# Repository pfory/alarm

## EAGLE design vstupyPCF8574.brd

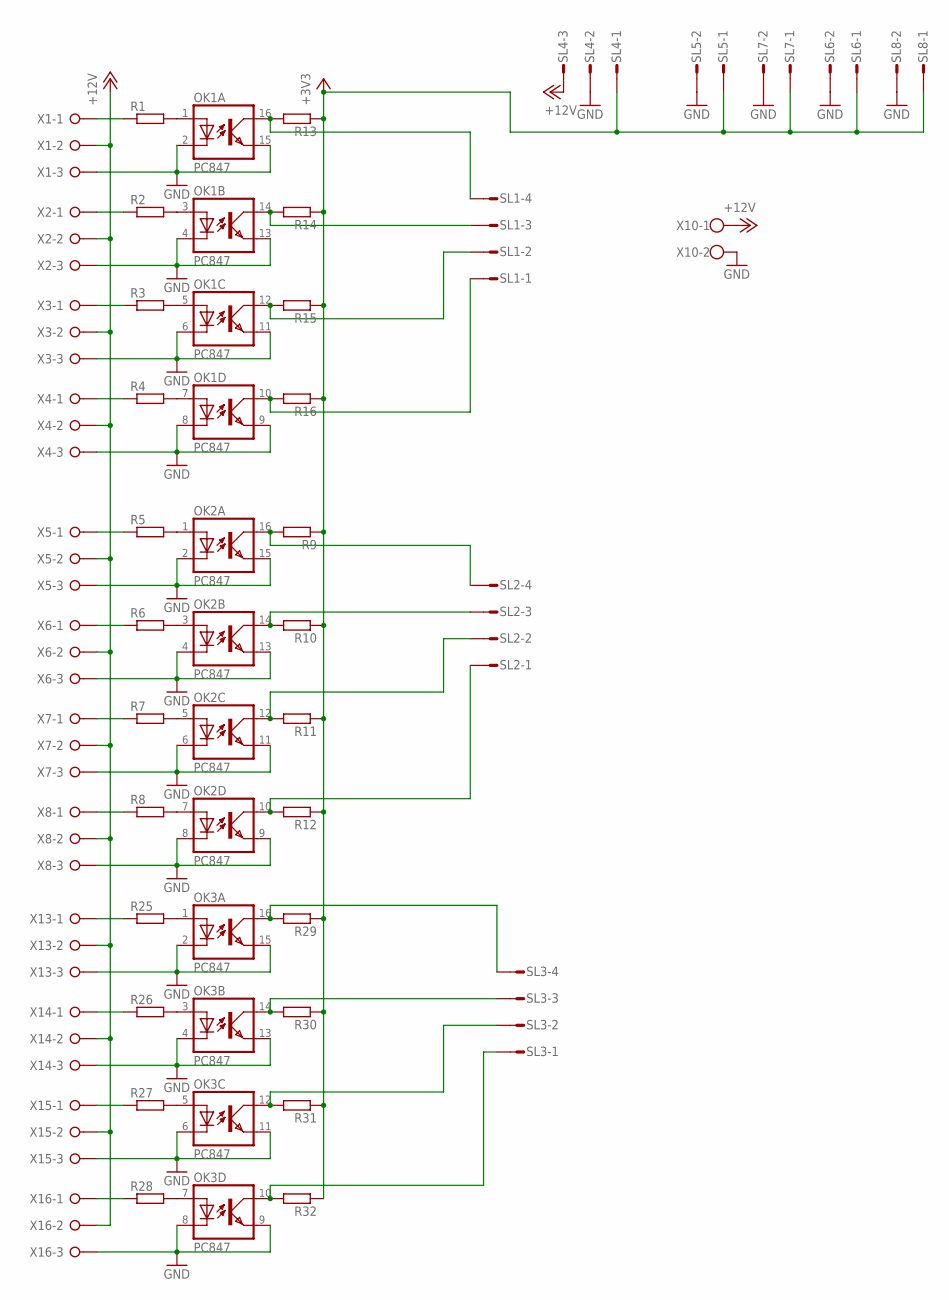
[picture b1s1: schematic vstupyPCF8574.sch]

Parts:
OK1, OK2, OK3: PC847; DIL16
R1, R2, R3, R4, R5, R6, R7, R8, R9, R10, R11, R12, R13, R14, R15, R16, R25, R26, R27, R28, R29, R30, R31, R32: R-EU_0204/5; 0204/5
SL1, SL2, SL3: M04S; 04P
SL4: M03S; 03P
SL5, SL6, SL7, SL8: M02S; 02P
X1, X2, X3, X4, X5, X6, X7, X8, X13, X14, X15, X16: W237-3E
X10: W237-102

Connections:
+3V3: R9.1, R10.1, R11.1, R12.1, R13.1, R14.1, R15.1, R16.1, R29.1, R30.1, R31.1, R32.1, SL4.1, SL5.1, SL6.1, SL7.1, SL8.1
+12V: SL4.3, X1.2, X2.2, X3.2, X4.2, X5.2, X6.2, X7.2, X8.2, X10.1, X13.2, X14.2, X15.2, X16.2
GND: OK1.2 (C), OK1.4 (C), OK1.6 (C), OK1.8 (C), OK1.9 (EMIT), OK1.11 (EMIT), OK1.13 (EMIT), OK1.15 (EMIT), OK2.2 (C), OK2.4 (C), OK2.6 (C), OK2.8 (C), OK2.9 (EMIT), OK2.11 (EMIT), OK2.13 (EMIT), OK2.15 (EMIT), OK3.2 (C), OK3.4 (C), OK3.6 (C), OK3.8 (C), OK3.9 (EMIT), OK3.11 (EMIT), OK3.13 (EMIT), OK3.15 (EMIT), SL4.2, SL5.2, SL6.2, SL7.2, SL8.2, X1.3, X2.3, X3.3, X4.3, X5.3, X6.3, X7.3, X8.3, X10.2, X13.3, X14.3, X15.3, X16.3
unnamed: OK1.1 (A), R1.2
unnamed: OK1.3 (A), R2.2
unnamed: OK1.5 (A), R3.2
unnamed: OK1.7 (A), R4.2
unnamed: OK2.1 (A), R5.2
unnamed: OK2.3 (A), R6.2
unnamed: OK2.5 (A), R7.2
unnamed: OK2.7 (A), R8.2
unnamed: R5.1, X5.1
unnamed: R6.1, X6.1
unnamed: R7.1, X7.1
unnamed: R8.1, X8.1
unnamed: R1.1, X1.1
unnamed: R2.1, X2.1
unnamed: R3.1, X3.1
unnamed: R4.1, X4.1
unnamed: OK2.16 (COL), R9.2, SL2.4
unnamed: OK2.14 (COL), R10.2, SL2.3
unnamed: OK2.12 (COL), R11.2, SL2.2
unnamed: OK2.10 (COL), R12.2, SL2.1
unnamed: OK1.16 (COL), R13.2, SL1.4
unnamed: OK1.14 (COL), R14.2, SL1.3
unnamed: OK1.12 (COL), R15.2, SL1.2
unnamed: OK3.16 (COL), R29.2, SL3.4
unnamed: OK3.14 (COL), R30.2, SL3.3
unnamed: OK3.12 (COL), R31.2, SL3.2
unnamed: OK3.10 (COL), R32.2, SL3.1
unnamed: OK1.10 (COL), R16.2, SL1.1
unnamed: OK3.1 (A), R25.2
unnamed: OK3.3 (A), R26.2
unnamed: OK3.5 (A), R27.2
unnamed: OK3.7 (A), R28.2
unnamed: R25.1, X13.1
unnamed: R26.1, X14.1
unnamed: R27.1, X15.1
unnamed: R28.1, X16.1

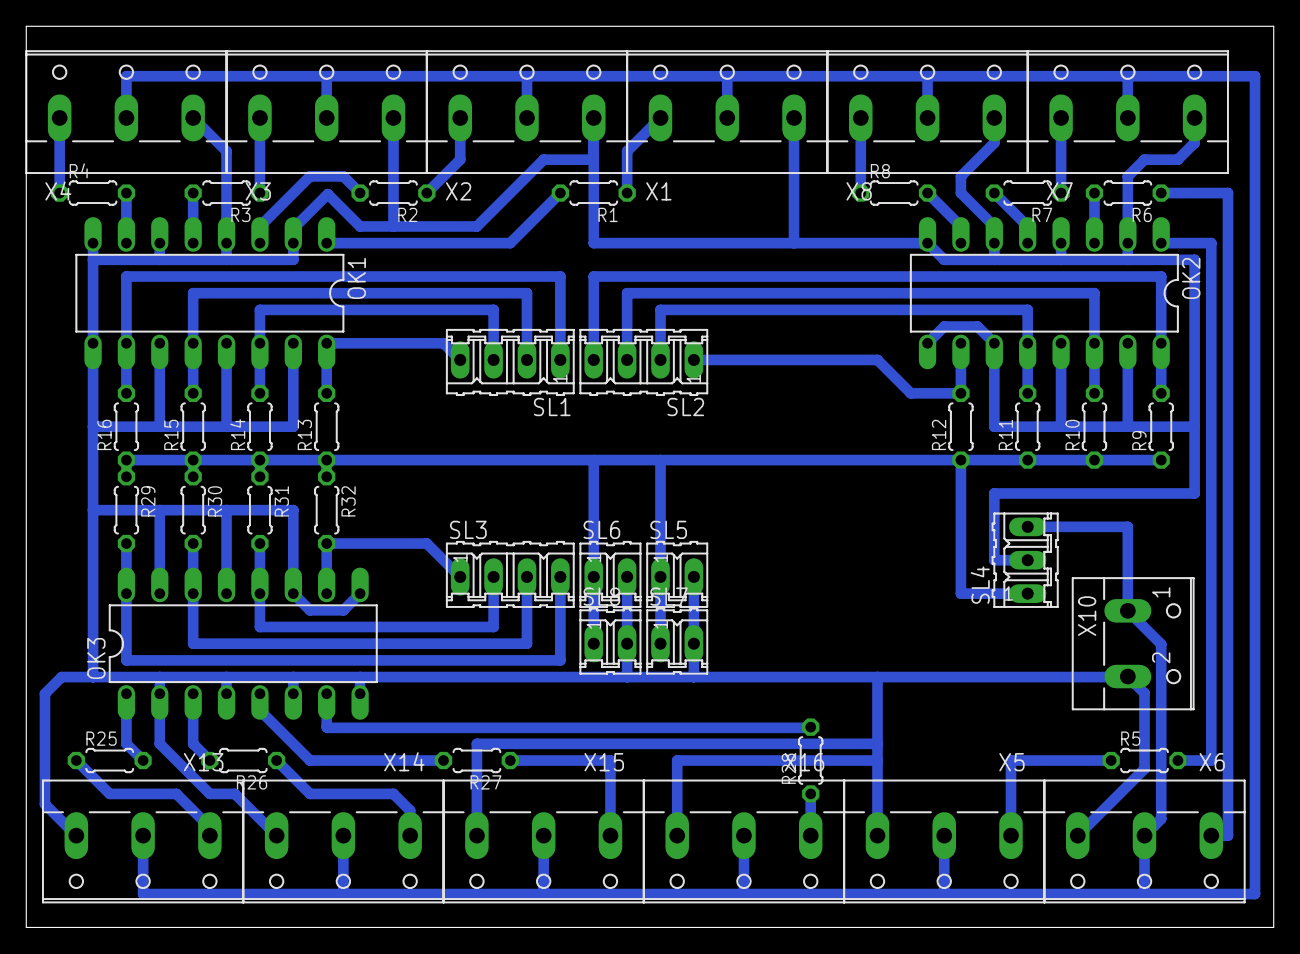
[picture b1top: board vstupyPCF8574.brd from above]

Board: 2 copper layers, 94.9 x 68.6 mm, 48 parts (0 on the bottom side), 39 nets.

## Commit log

2016-04-22 init
2016-04-25 +popis
2016-12-17 +pir
2016-12-19 uprava
2016-12-22 +mqtt
2018-06-28 znovuvskriseni projektu
2018-06-28 uprava desky
2018-06-28 + knihovna esp
2018-11-27 popis + htm
2018-11-30 subscribe
